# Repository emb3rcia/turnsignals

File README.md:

# turnsignals

Hello! This project is very simple, but to some people may be very needed, this is turnsignals module for PC steering wheels like logitech g29, made for HackClub's Blueprint program. It features USB-C (USB-FS standard) port for data and power and ESD protection on VBUS, DATA channels and CC channels! Firmware is given as whole STM32CubeIDE project. It is generated in STM32CubeMX and then the rest written in STM32CubeIDE

## Why i did this?

I want to get driving license soon. My biggest fear? Getting ticket for forgotting to signal a turn. My solution? Buy used PC steering wheel with pedals and gear shifter, make my own turnsignals and download some game where i can drive and use them. In this way i can make it my muscle memory.

# Images

Schematic

PCB

3D KiCad viewer

3D PCB

3D Assembled

3D Lever

3D Case (top)

3D Case (bottom)

# Datasheets & part list
Here you can find datasheet for every part and exact part number for it i used:
- MCU: [STM Electronics STM32F042K6T6 LQFP-32 Package](Datasheets/STM32F042K6T6.pdf)
- USB-C Port: [SHOU HAN TYPE-C 16PIN 2MD(073)](Datasheets/TYPE-C-16PIN-2MD(073).pdf)
- DATA and CC lines ESD diodes: [Semtech RCLAMP0502BATCT](Datasheets/RCLAMP0502BATCT.pdf)
- VBUS line ESD diode: [Yageo SMA6L5.0A_TR13](Datasheets/SMA6L5.0A_TR13.pdf)
- 3.3V LDO: [Microchip MCP1726-3302E_SNVAO](Datasheets/MCP1726-3302E_SNVAO.pdf)
- 4.7uF 16V Capacitor: [Murata Electronics GRM188Z71C475KE21D](Datasheets/GRM188Z71C475KE21D.pdf)
- 1uF 10V Capacitor: Samsung Electro-Mechanics CL10A105KA8NNNC
- 100nF 10V Capacitor: [Vishay VJ0603Y104JXQCW1BC](Datasheets/VJ0603Y104JXQCW1BC.pdf)
- 5.1kOhm 0.1W Resistor: [Bourns CR0603-FX-5101ELF](Datasheets/CR0603-FX-5101ELF.pdf)
- 10Ohm 0.1W Resistor: [Vishay CRCW060310K0DHEAP](Datasheets/CRCW060310K0DHEAP.pdf)
- 300Ohm 0.1W Resistor: [GiantOhm GR0603J330RT5G00](Datasheets/GR0603J330RT5G00.pdf)
- BOOT button: [SHOU HAN TS6643TP 250gf 009](Datasheets/TS6643TP-250gf-009.pdf)
- Lever Toggle switch: [Dailywell 1MS1T1B1M1QES-5](Datasheets/1MS1T1B1M1QES-5.pdf)
# BOM
|Item                                     |Description                 |Needed|Ordered|Why more/less?                   |Unit Price ($)|Total Price ($) |URL                                                                   |
|-----------------------------------------|----------------------------|------|-------|---------------------------------|--------------|----------------|----------------------------------------------------------------------|
|ST STM32F042K6T6                         |MCU                         |1     |1      |-                                |1.80$         |1.80$           |https://www.lcsc.com/product-detail/C69216.html                       |
|SEMTECH RCLAMP0502BATCT                  |CC and DATA lines esd       |2     |0      |I have 3 left from other project |-             |-               |https://www.lcsc.com/product-detail/C117553.html                      |
|Littelfuse SMA6L5.0A                     |VBUS line esd               |1     |1      |-                                |0.79$         |0.79$           |https://www.lcsc.com/product-detail/C1974860.html                     |
|MICROCHIP MCP1726-3302E/SN               |3.3V LDO                    |1     |1      |-                                |2.22$         |2.22$           |https://www.lcsc.com/product-detail/C635928.html                      |
|muRata GRM188Z71C475KE21D                |4.7uF capacitor             |1     |0      |I have 9 left from other project |-             |-               |https://www.lcsc.com/product-detail/C389010.html                      |
|Samsung Electro-Mechanics CL10A105KA8NNNC|1uF capacitor               |2     |50     |Minimal order size is 50         |0.0058$       |0.29$           |https://www.lcsc.com/product-detail/C5673.html                        |
|VISHAY VJ0603Y104JXQCW1BC                |100nF decap capacitor       |4     |5      |sold in increments of 5          |0.08$         |0.40$           |https://www.lcsc.com/product-detail/C3834925.html                     |
|SAMWHA CS1608X7R225K100NRB               |2.2uF capacitor             |2     |0      |I have 98 left from other project|-             |-               |https://www.lcsc.com/product-detail/C516003.html                      |
|BOURNS CR0603-FX-5101ELF                 |5.1kOhm 0.1w CC resistor    |2     |0      |I have 8 left from other project |-             |-               |https://www.lcsc.com/product-detail/C2076779.html                     |
|VISHAY CRCW060310K0DHEAP                 |10kOhm pull-up/down resistor|2     |0      |I have 3 left from other project |-             |-               |https://www.lcsc.com/product-detail/C3917708.html                     |
|SHOU HAN TS6643TP 250gf 009              |BOOT and NRST button        |2     |0      |I have 48 left from other project|-             |-               |https://www.lcsc.com/product-detail/C5342967.html                     |
|SHOU HAN TYPE-C 16PIN 2MD(073)           |USB-C plug                  |1     |0      |I have 19 left from other project|-             |-               |https://www.lcsc.com/product-detail/C2765186.html                     |
|Shuntian PB1.6X4                         |Mouting screws              |4     |10     |minimal order size is 10         |0.04$         |0.42$           |https://www.lcsc.com/product-detail/C357374.html?s_z=n_1.6x4          |
|Dailywell 1MS1T1B1M1QES-5                |Lever Toggle switch         |1     |1      |-                                |1.01$         |1.01$           |https://www.lcsc.com/product-detail/C496154.html?s_z=n_1MS1T1B1M1QES-5|
|PCB                                      |PCB                         |1     |5      |5 is minimal order amount        |-             |2$+1.5$ delivery|https://jlcpcb.com/                                                   |

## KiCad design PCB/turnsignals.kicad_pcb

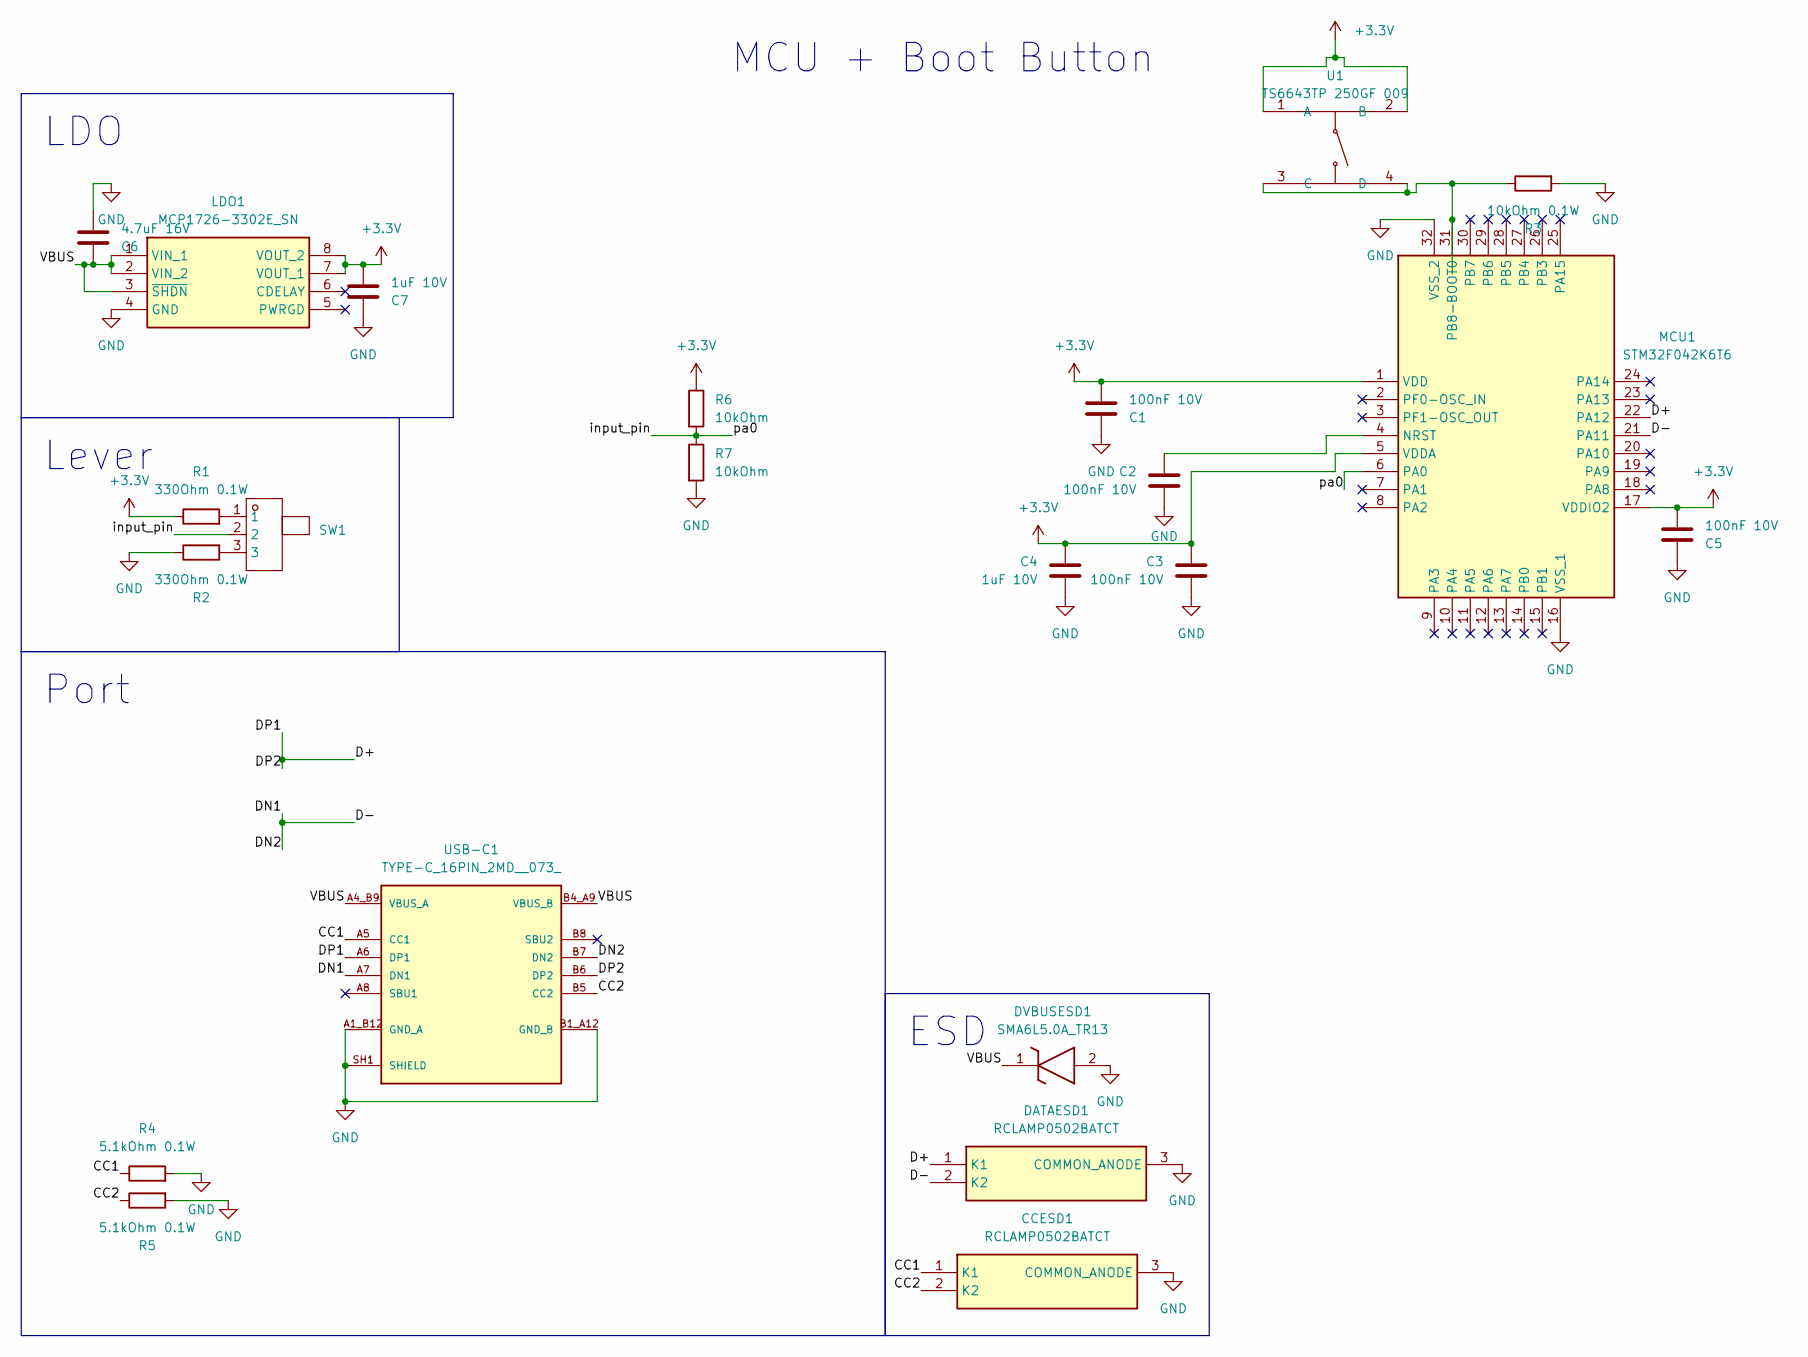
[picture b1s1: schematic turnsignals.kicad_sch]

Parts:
C1, C2, C3, C5: 100nF 10V; C_0603_1608Metric_Pad1.08x0.95mm_HandSolder
C4, C7: 1uF 10V; C_0603_1608Metric_Pad1.08x0.95mm_HandSolder
C6: 4.7uF 16V; C_0603_1608Metric_Pad1.08x0.95mm_HandSolder
CCESD1: RCLAMP0502BATCT; SOT50P160X90-3N; Manufacturer_Part_Number RCLAMP0502BATCT; Mouser Part Number 947-RCLAMP0502BATCT
DATAESD1: RCLAMP0502BATCT; SOT50P160X90-3N; Manufacturer_Part_Number RCLAMP0502BATCT; Mouser Part Number 947-RCLAMP0502BATCT
DVBUSESD1: SMA6L5.0A_TR13; SODFL4626X140N; Manufacturer_Part_Number SMA6L5.0A/TR13
LDO1: MCP1726-3302E_SN; SOIC127P600X175-8N; Manufacturer_Part_Number MCP1726-3302E/SN; Mouser Part Number 579-MCP1726-3302E/SN
MCU1: STM32F042K6T6; QFP80P900X900X160-32N; Manufacturer_Part_Number STM32F042K6T6; Mouser Part Number 511-STM32F042K6T6
R1, R2: 330Ohm 0.1W; R_0603_1608Metric_Pad0.98x0.95mm_HandSolder
R3: 10kOhm 0.1W; R_0603_1608Metric_Pad0.98x0.95mm_HandSolder
R4, R5: 5.1kOhm 0.1W; R_0603_1608Metric_Pad0.98x0.95mm_HandSolder
R6, R7: 10kOhm; R_0603_1608Metric_Pad0.98x0.95mm_HandSolder
SW1: SW-TH_1MS1T1B1M1QES-5
U1: TS6643TP 250GF 009; SW-SMD_4P-L6.2-W6.0-P4.50-LS9.0; LCSC Part C5342967
USB-C1: TYPE-C_16PIN_2MD__073_; SHOUHAN_TYPE-C_16PIN_2MD__073_; PARTREV A

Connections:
+3.3V: C1.2, C3.1, C4.1, C5.2, C7.2, LDO1.7 (VOUT_1), LDO1.8 (VOUT_2), MCU1.1 (VDD), MCU1.5 (VDDA), MCU1.17 (VDDIO2), R1.1, R6.1, U1.1 (A), U1.2 (B)
/CC1: CCESD1.1 (K1), R4.1, USB-C1.A5 (CC1)
/CC2: CCESD1.2 (K2), R5.1, USB-C1.B5 (CC2)
/D+: DATAESD1.1 (K1), MCU1.22 (PA12), USB-C1.A6 (DP1), USB-C1.B6 (DP2)
/D-: DATAESD1.2 (K2), MCU1.21 (PA11), USB-C1.A7 (DN1), USB-C1.B7 (DN2)
/VBUS: C6.1, DVBUSESD1.1 (K), LDO1.1 (VIN_1), LDO1.2 (VIN_2), LDO1.3 (~SHDN), USB-C1.A4_B9 (VBUS_A), USB-C1.B4_A9 (VBUS_B)
/input_pin: MCU1.6 (PA0), R6.2, R7.1, SW1.2
GND: C1.1, C2.2, C3.2, C4.2, C5.1, C6.2, C7.1, CCESD1.3 (COMMON_ANODE), DATAESD1.3 (COMMON_ANODE), DVBUSESD1.2 (A), LDO1.4 (GND), MCU1.16 (VSS_1), MCU1.32 (VSS_2), R2.1, R3.2, R4.2, R5.2, R7.2, USB-C1.A1_B12 (GND_A), USB-C1.B1_A12 (GND_B), USB-C1.SH1 (SHIELD), USB-C1.SH2 (SHIELD), USB-C1.SH3 (SHIELD), USB-C1.SH4 (SHIELD)
unnamed: C2.1, MCU1.4 (NRST)
unnamed: MCU1.31 (PB8-BOOT0), R3.1, U1.3 (C), U1.4 (D)
unnamed: R1.2, SW1.1
unnamed: R2.2, SW1.3

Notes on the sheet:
MCU + Boot Button
Port
ESD
LDO
Lever

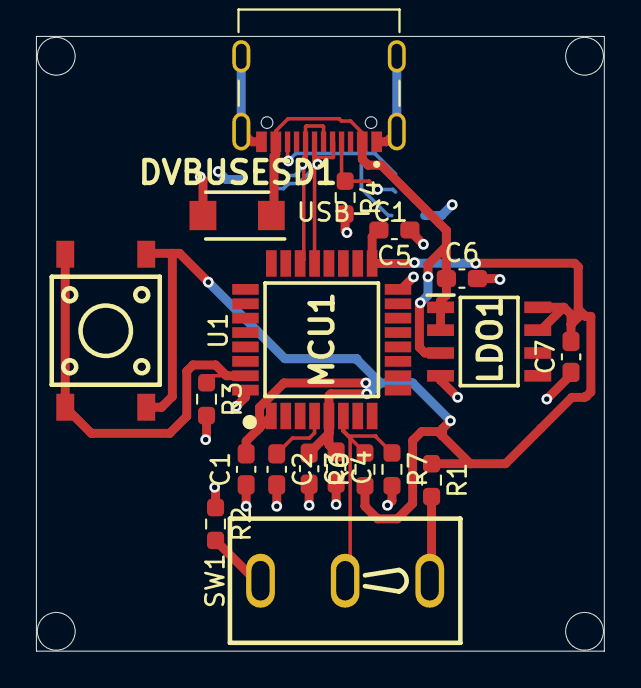
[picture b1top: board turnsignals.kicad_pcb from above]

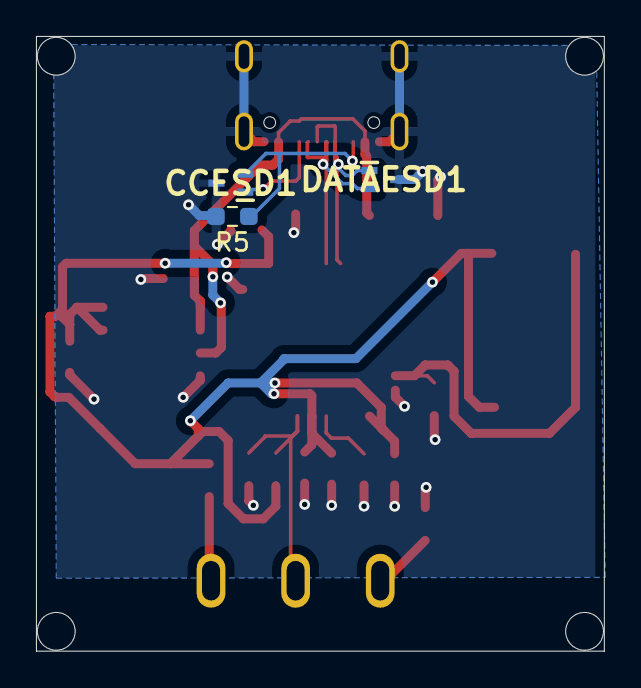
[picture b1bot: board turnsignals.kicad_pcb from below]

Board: 2 copper layers, 31.5 x 34.1 mm, 22 parts (3 on the bottom side), 12 nets.

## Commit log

2026-02-01 Added datasheets, images, pcb files, 3d files, BOM and readme
2026-02-01 added 3d files
2026-02-01 updated 3d files
2026-02-01 push
2026-02-01 Added firmware
2026-02-04 Corrected button wiring
2026-02-14 Added f3d files
2026-02-14 Update README with project details and images
2026-02-14 last commit i didint remove the integrated copilot message, sorry!
2026-02-14 Added the purpose of creation of this project
2026-02-19 Added gerbers
2026-02-19 Updated bom
2026-02-19 Changed README.md
